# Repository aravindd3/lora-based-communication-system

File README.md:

## Project Team

* [Aravind VS](https://github.com/USERNAME)
* [Vyshnav Harilal](https://github.com/USERNAME)
* [Sidharth P](https://github.com/USERNAME)
* [Jagadjith U](https://github.com/Jagadjith-U)
* [Arun K](https://github.com/USERNAME)
* [Alwin Sunny Jude](https://github.com/Jude-00-05)

# LoRa-Based Communication System

Repository for the firmware and custom KiCad hardware design of a portable LoRa-based communication device.

## Repository layout

- `firmware/` — ESP32/Arduino sketches.
- `hardware/kicad/` — editable KiCad project and required local libraries.
- `hardware/review/` — ERC/DRC reports and schematic/PCB review exports.
- `docs/` — project documentation.

## Hardware design

Open `hardware/kicad/lora.kicad_pro` in KiCad. Keep the `libraries/` folder and the `sym-lib-table` and `fp-lib-table` files beside the project files; they provide the custom symbols and footprints needed by the design.

The supplied board package includes editable schematic and PCB files, local libraries, review PDFs, and ERC/DRC results. It does not include production Gerber or drill files.

## Firmware

The `firmware/` folder contains the available Arduino sketches for microphone, OLED interface, push-to-talk, and LoRa-control functions. Each sketch is in a folder matching its `.ino` filename so it can be opened in the Arduino IDE.

## Important hardware note

The supplied KiCad design uses an ESP32-S3-WROOM-1 footprint and an Ai-Thinker Ra-01-derived LoRa footprint. Confirm the actual populated modules, pin assignments, and component values against the assembled board before any new hardware revision or fabrication order.

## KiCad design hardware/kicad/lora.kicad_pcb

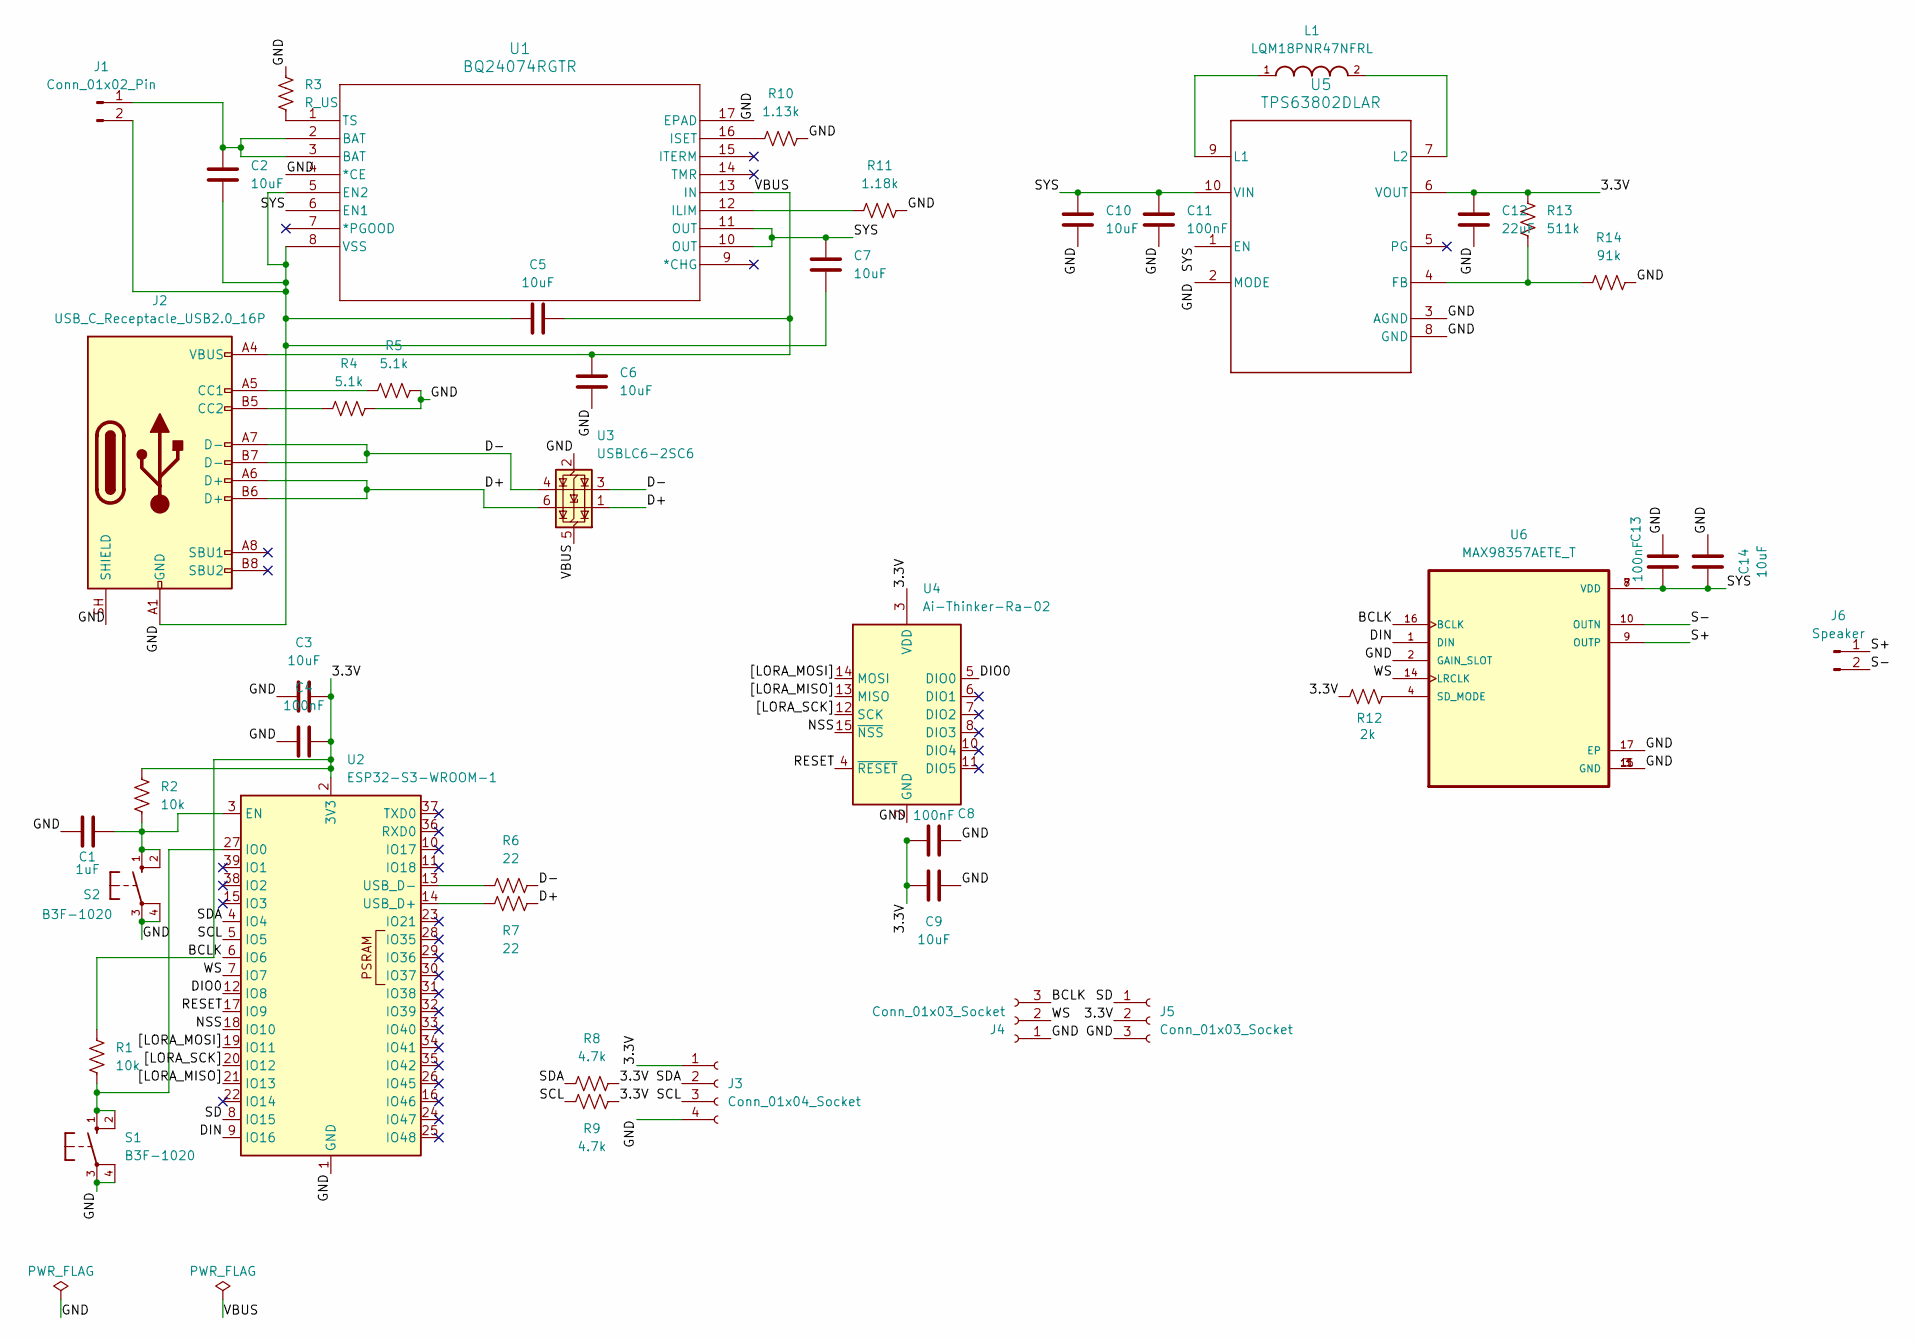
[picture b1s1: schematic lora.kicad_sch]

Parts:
C1: 1uF; C_1206_3216Metric_C1
C2: 10uF; C_0805_2012Metric_C2
C3: 10uF; C_0805_2012Metric_C3
C4: 100nF; C_0603_1608Metric_C4
C5: 10uF; C_0805_2012Metric_C5
C6: 10uF; C_0805_2012Metric_C6
C7: 10uF; C_0805_2012Metric_C7
C8: 100nF; C_0603_1608Metric_C8
C9: 10uF; C_0805_2012Metric_C9
C10: 10uF; C_0805_2012Metric_C10
C11: 100nF; C_0603_1608Metric_C11
C12: 22uF; C_1206_3216Metric_C12
C13: 100nF; C_0603_1608Metric_C13
C14: 10uF; C_0805_2012Metric_C14
J1: Conn_01x02_Pin; PinHeader_1x02_P2.54mm_Vertical_J1
J2: USB_C_Receptacle_USB2.0_16P; USB_C_Receptacle_GCT_USB4105-xx-A_16P_TopMnt_Horizontal_J2
J3: Conn_01x04_Socket; PinSocket_1x04_P2.54mm_Vertical_J3
J4: Conn_01x03_Socket; PinSocket_1x03_P2.54mm_Vertical_J4
J5: Conn_01x03_Socket; PinSocket_1x03_P2.54mm_Vertical_J5
J6: Speaker; PinHeader_1x02_P2.54mm_Vertical_J6
L1: LQM18PNR47NFRL; INDC1608X95N_L1
R1: 10k; R_0603_1608Metric_R1
R2: 10k; R_0603_1608Metric_R2
R3: R_US; R_0603_1608Metric_R3
R4: 5.1k; R_0603_1608Metric_R4
R5: 5.1k; R_0603_1608Metric_R5
R6: 22; R_0603_1608Metric_R6
R7: 22; R_0603_1608Metric_R7
R8: 4.7k; R_0603_1608Metric_R8
R9: 4.7k; R_0603_1608Metric_R9
R10: 1.13k; R_0603_1608Metric_R10
R11: 1.18k; R_0603_1608Metric_R11
R12: 2k; R_0603_1608Metric_R12
R13: 511k; R_0603_1608Metric_R13
R14: 91k; R_0603_1608Metric_R14
S1: B3F-1020; B3F-1020_S1; MPN B3F-1000
S2: B3F-1020; B3F-1020_S2; MPN B3F-1000
U1: BQ24074RGTR; RGT16_1P7X1P7_U1
U2: ESP32-S3-WROOM-1; ESP32-S3-WROOM-1_U2
U3: USBLC6-2SC6; SOT-23-6_U3
U4: Ai-Thinker-Ra-02; Ai-Thinker-Ra-01-LoRa_U4
U5: TPS63802DLAR; DLA0010A_U5
U6: MAX98357AETE_T; QFN50P300X300X80-17N_U6; DigiKey_Part_Number MAX98357AETE+TCT-ND

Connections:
/3.3V: C3.1, C4.1, C8.1, C9.1, C12.1, J3.1, J5.2, R1.1, R2.1, R8.2, R9.2, R12.1, R13.1, U2.2 (3V3), U4.3 (VDD), U5.6 (VOUT)
/BCLK: J4.3, U2.6 (IO6), U6.16 (BCLK)
/D+: J2.A6 (D+), J2.B6 (D+), R7.1, U3.1 (I/O1), U3.6 (I/O1)
/D-: J2.A7 (D-), J2.B7 (D-), R6.1, U3.3 (I/O2), U3.4 (I/O2)
/DIN: U2.9 (IO16), U6.1 (DIN)
/DIO0: U2.12 (IO8), U4.5 (DIO0)
/GND: C1.1, C2.2, C3.2, C4.2, C5.1, C6.2, C7.1, C8.2, C9.2, C10.2, C11.2, C12.2, C13.2, C14.2, J1.2, J2.A1 (GND), J2.A12 (GND), J2.B1 (GND), J2.B12 (GND), J2.SH (SHIELD), J3.4, J4.1, J5.3, R3.2, R4.1, R5.2, R10.2, R11.2, R14.2, S1.3, S1.4, S2.3, S2.4, U1.4 (*CE), U1.5 (EN2), U1.8 (VSS), U1.17 (EPAD), U2.1 (GND), U2.40 (GND), U2.41 (GND), U3.2 (GND), U4.1 (GND), U4.2 (GND), U4.9 (GND), U4.16 (GND), U5.2 (MODE), U5.3 (AGND), U5.8 (GND), U6.2 (GAIN_SLOT), U6.3 (GND), U6.11 (GND), U6.15 (GND), U6.17 (EP)
/NSS: U2.18 (IO10), U4.15 (~NSS)
/RESET: U2.17 (IO9), U4.4 (~RESET)
/S+: J6.1, U6.9 (OUTP)
/S-: J6.2, U6.10 (OUTN)
/SCL: J3.3, R9.1, U2.5 (IO5)
/SD: J5.1, U2.8 (IO15)
/SDA: J3.2, R8.1, U2.4 (IO4)
/SYS: C7.2, C10.1, C11.1, C13.1, C14.1, U1.6 (EN1), U1.10 (OUT), U1.11 (OUT), U5.1 (EN), U5.10 (VIN), U6.7 (VDD), U6.8 (VDD)
/VBUS: C5.2, C6.1, J2.A4 (VBUS), J2.A9 (VBUS), J2.B4 (VBUS), J2.B9 (VBUS), U1.13 (IN), U3.5 (VBUS)
/WS: J4.2, U2.7 (IO7), U6.14 (LRCLK)
/[LORA_MISO]: U2.21 (IO13), U4.13 (MISO)
/[LORA_MOSI]: U2.19 (IO11), U4.14 (MOSI)
/[LORA_SCK]: U2.20 (IO12), U4.12 (SCK)
unnamed: C2.1, J1.1, U1.2 (BAT), U1.3 (BAT)
unnamed: J2.A5 (CC1), R5.1
unnamed: J2.B5 (CC2), R4.2
unnamed: R11.1, U1.12 (ILIM)
unnamed: R10.1, U1.16 (ISET)
unnamed: R3.1, U1.1 (TS)
unnamed: C1.2, R2.2, S2.1, S2.2, U2.3 (EN)
unnamed: R1.2, S1.1, S1.2, U2.27 (IO0)
unnamed: R7.2, U2.14 (USB_D+)
unnamed: R6.2, U2.13 (USB_D-)
unnamed: R13.2, R14.1, U5.4 (FB)
unnamed: L1.1, U5.9 (L1)
unnamed: L1.2, U5.7 (L2)
unnamed: R12.2, U6.4 (SD_MODE)

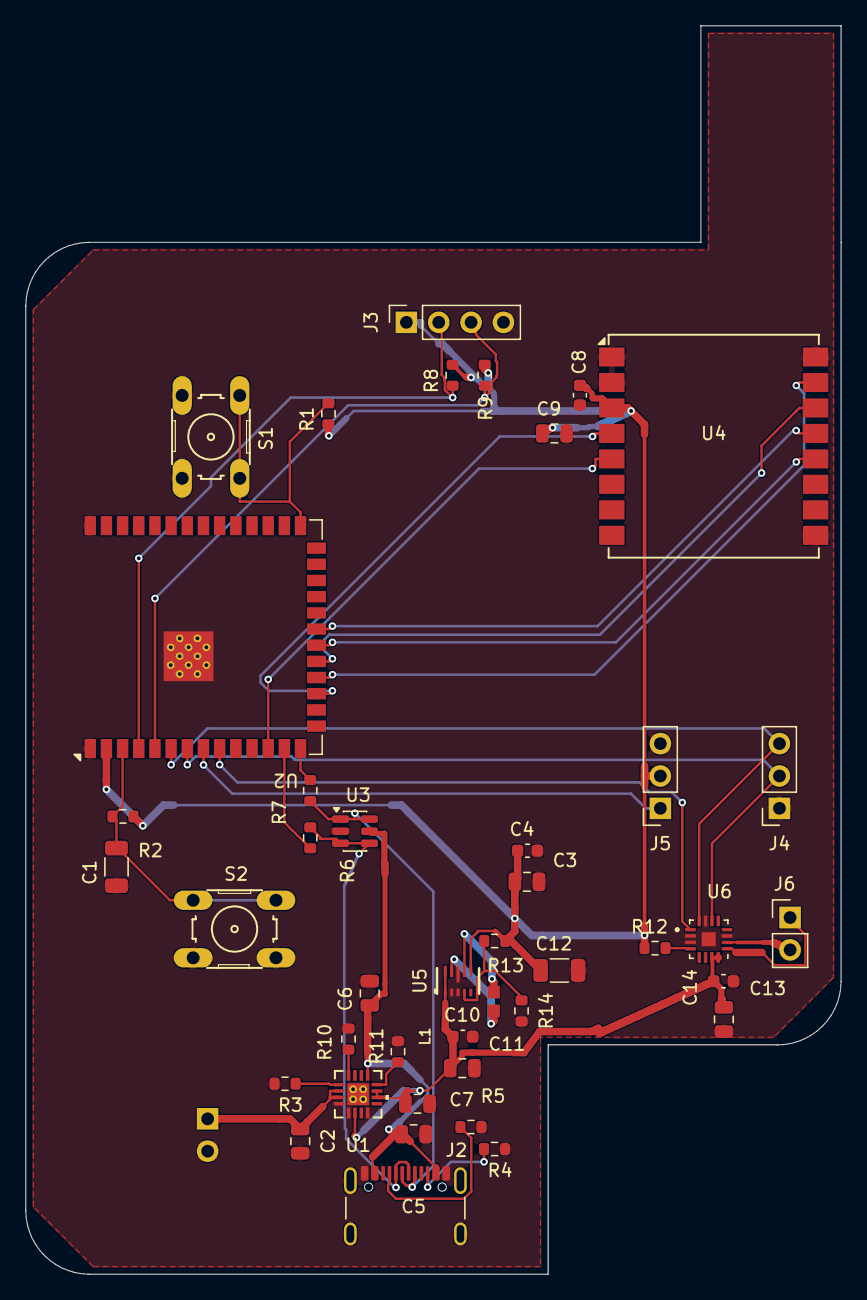
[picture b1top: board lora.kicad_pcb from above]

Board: 2 copper layers, 64.0 x 98.0 mm, 43 parts (1 on the bottom side), 34 nets.
